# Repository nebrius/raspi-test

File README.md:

# raspi-test
A sample project for testing out Raspi IO on-device. Like a manual integration test, but a complete project.

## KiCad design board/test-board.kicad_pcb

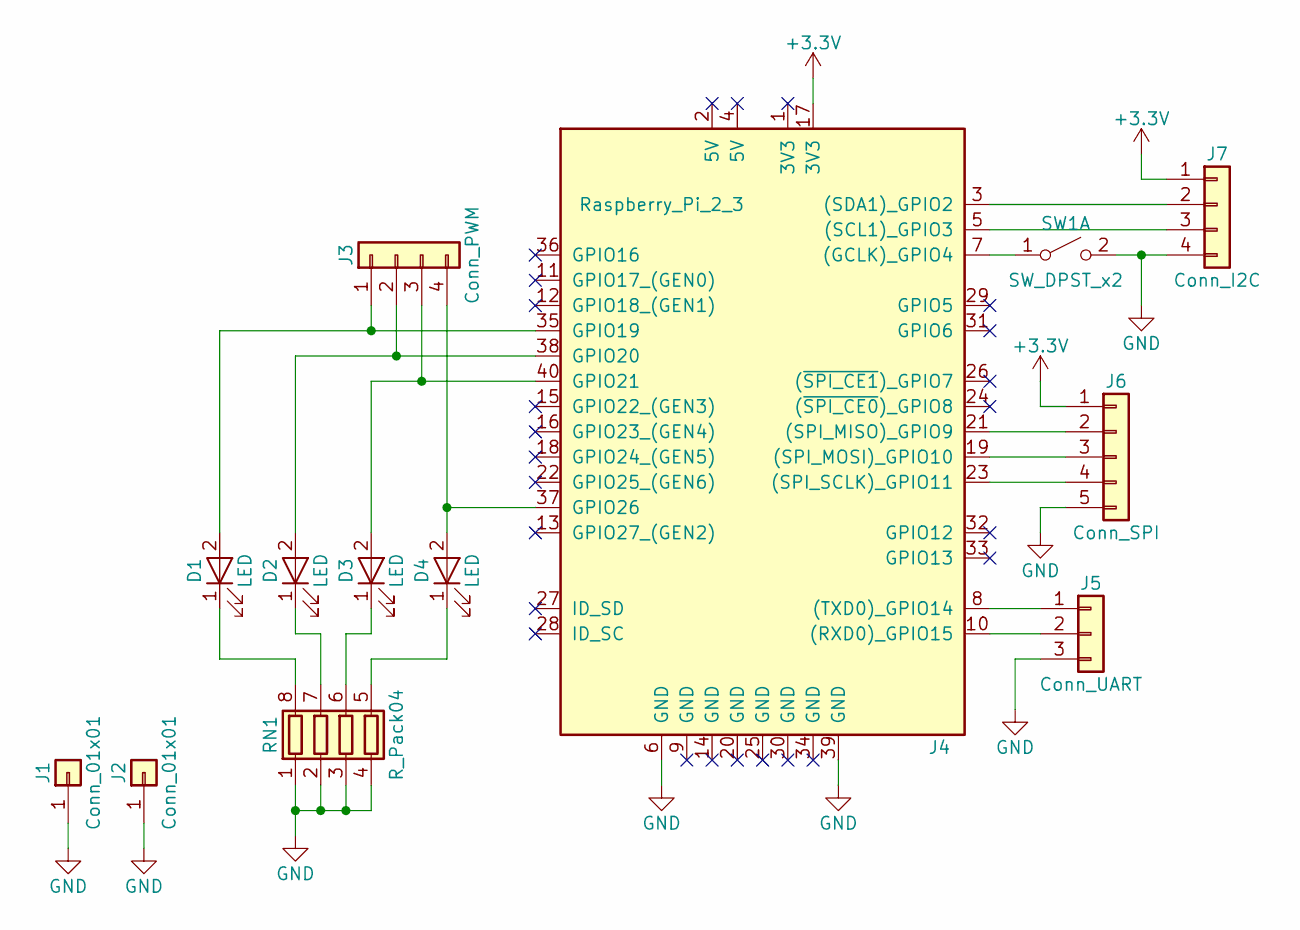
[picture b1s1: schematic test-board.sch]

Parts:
D1, D2, D3, D4: LED; LED_D5.0mm
J1, J2: Conn_01x01; Pin_Header_Straight_1x01_Pitch2.54mm
J3: Conn_PWM; Pin_Header_Straight_1x04_Pitch2.54mm
J4: Raspberry_Pi_2_3; Pin_Header_Straight_2x20_Pitch2.54mm
J5: Conn_UART; Pin_Header_Straight_1x03_Pitch2.54mm
J6: Conn_SPI; Pin_Header_Straight_1x05_Pitch2.54mm
J7: Conn_I2C; Pin_Header_Straight_1x04_Pitch2.54mm
RN1: R_Pack04; R_Array_Concave_4x2012.kicad_mod
SW1: SW_DPST_x2

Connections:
+3V3: J4.17 (3V3), J6.1, J7.1
GND: J1.1, J2.1, J4.6 (GND), J4.39 (GND), J5.3, J6.5, J7.4, RN1.1 (R1.1), RN1.2 (R2.1), RN1.3 (R3.1), RN1.4 (R4.1), SW1.2 (B)
unnamed: D1.1 (K), RN1.8 (R1.2)
unnamed: D1.2 (A), J3.1, J4.35 (GPIO19)
unnamed: D2.1 (K), RN1.7 (R2.2)
unnamed: D2.2 (A), J3.2, J4.38 (GPIO20)
unnamed: D3.1 (K), RN1.6 (R3.2)
unnamed: D3.2 (A), J3.3, J4.40 (GPIO21)
unnamed: D4.1 (K), RN1.5 (R4.2)
unnamed: D4.2 (A), J3.4, J4.37 (GPIO26)
unnamed: J4.3 ((SDA1)_GPIO2), J7.2
unnamed: J4.5 ((SCL1)_GPIO3), J7.3
unnamed: J4.7 ((GCLK)_GPIO4), SW1.1 (A)
unnamed: J4.8 ((TXD0)_GPIO14), J5.1
unnamed: J4.10 ((RXD0)_GPIO15), J5.2
unnamed: J4.19 ((SPI_MOSI)_GPIO10), J6.3
unnamed: J4.21 ((SPI_MISO)_GPIO9), J6.2
unnamed: J4.23 ((SPI_SCLK)_GPIO11), J6.4

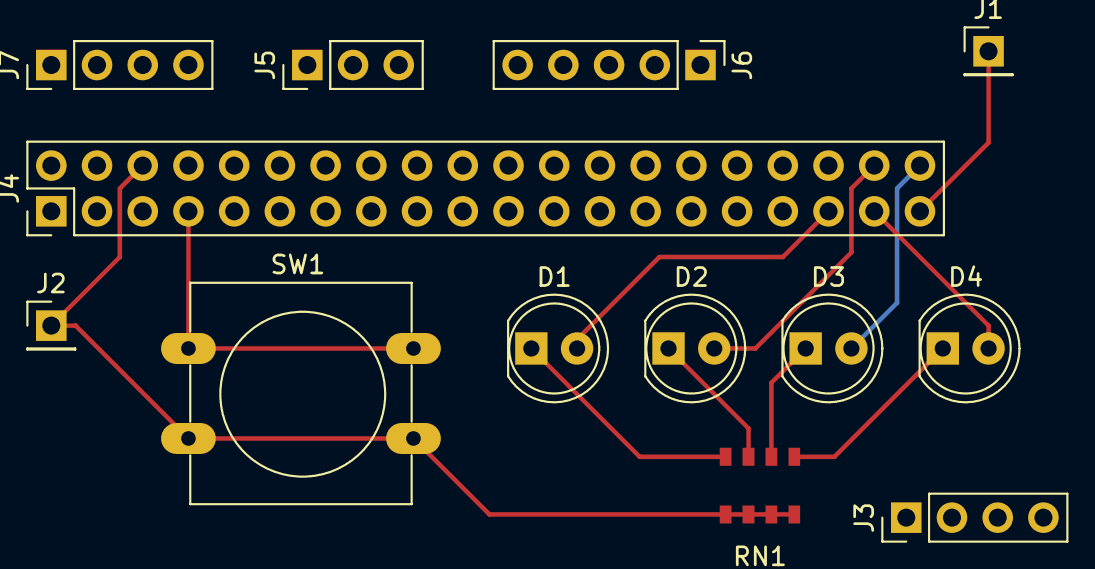
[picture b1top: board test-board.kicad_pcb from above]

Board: 2 copper layers, 13 parts (0 on the bottom side), 18 nets.

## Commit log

2018-09-11 Initial test file
2018-09-11 Implemented first integration test
2018-09-12 Started creating board schematic
2018-09-12 Added PWM tests
2018-09-13 More work on fleshing out test board
2019-02-12 Almost done with tests
2019-02-21 Finished raspi-test for raspi-io 10
2019-04-19 Added testing multiple PWM pins, some with native hardware support, some without
